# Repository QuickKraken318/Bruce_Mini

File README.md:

Original project: https://github.com/pr3y

Not tested IRL yet

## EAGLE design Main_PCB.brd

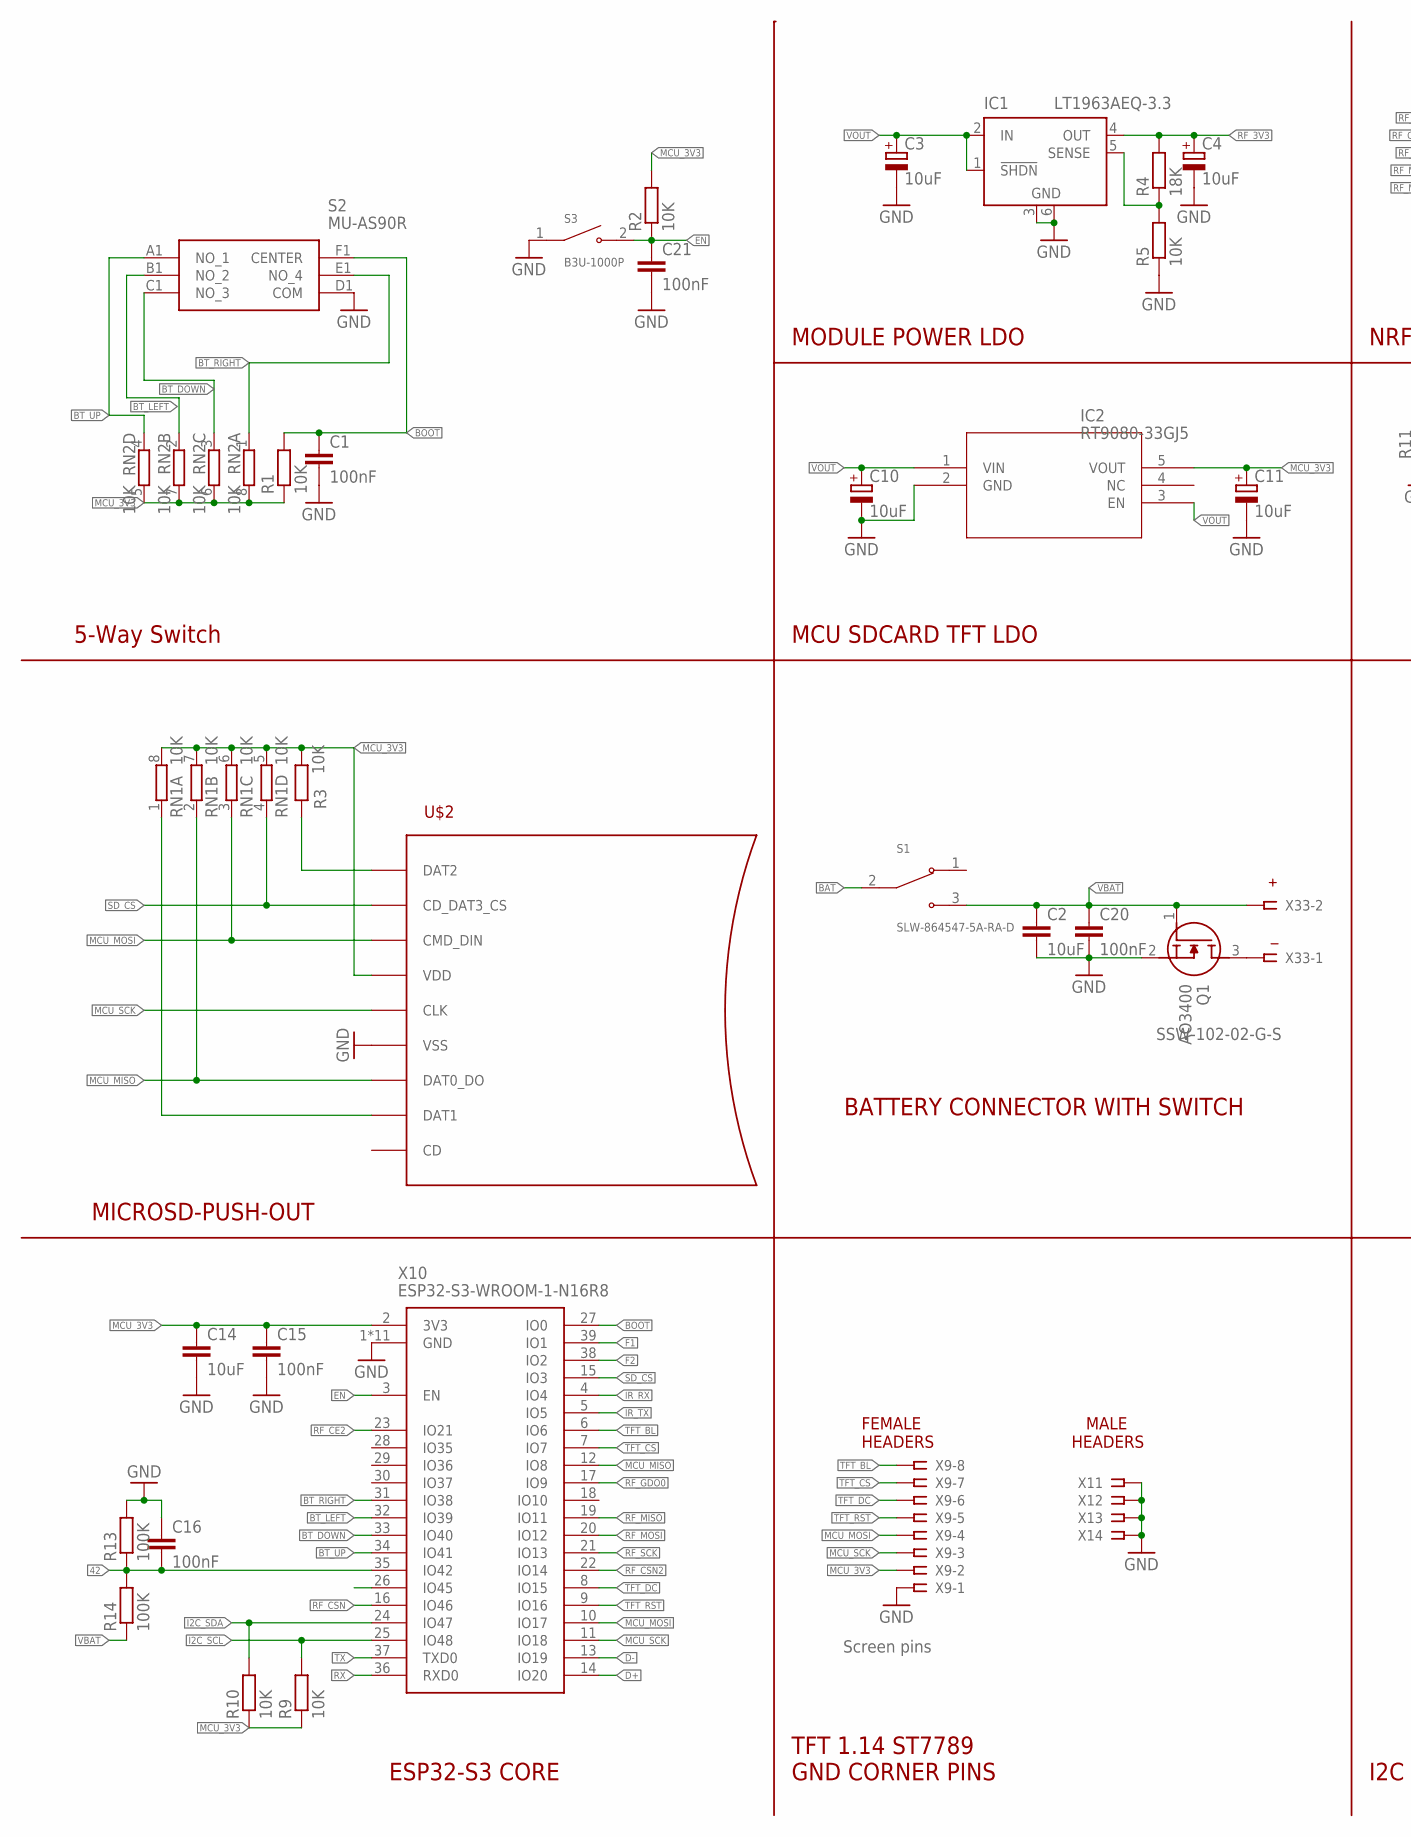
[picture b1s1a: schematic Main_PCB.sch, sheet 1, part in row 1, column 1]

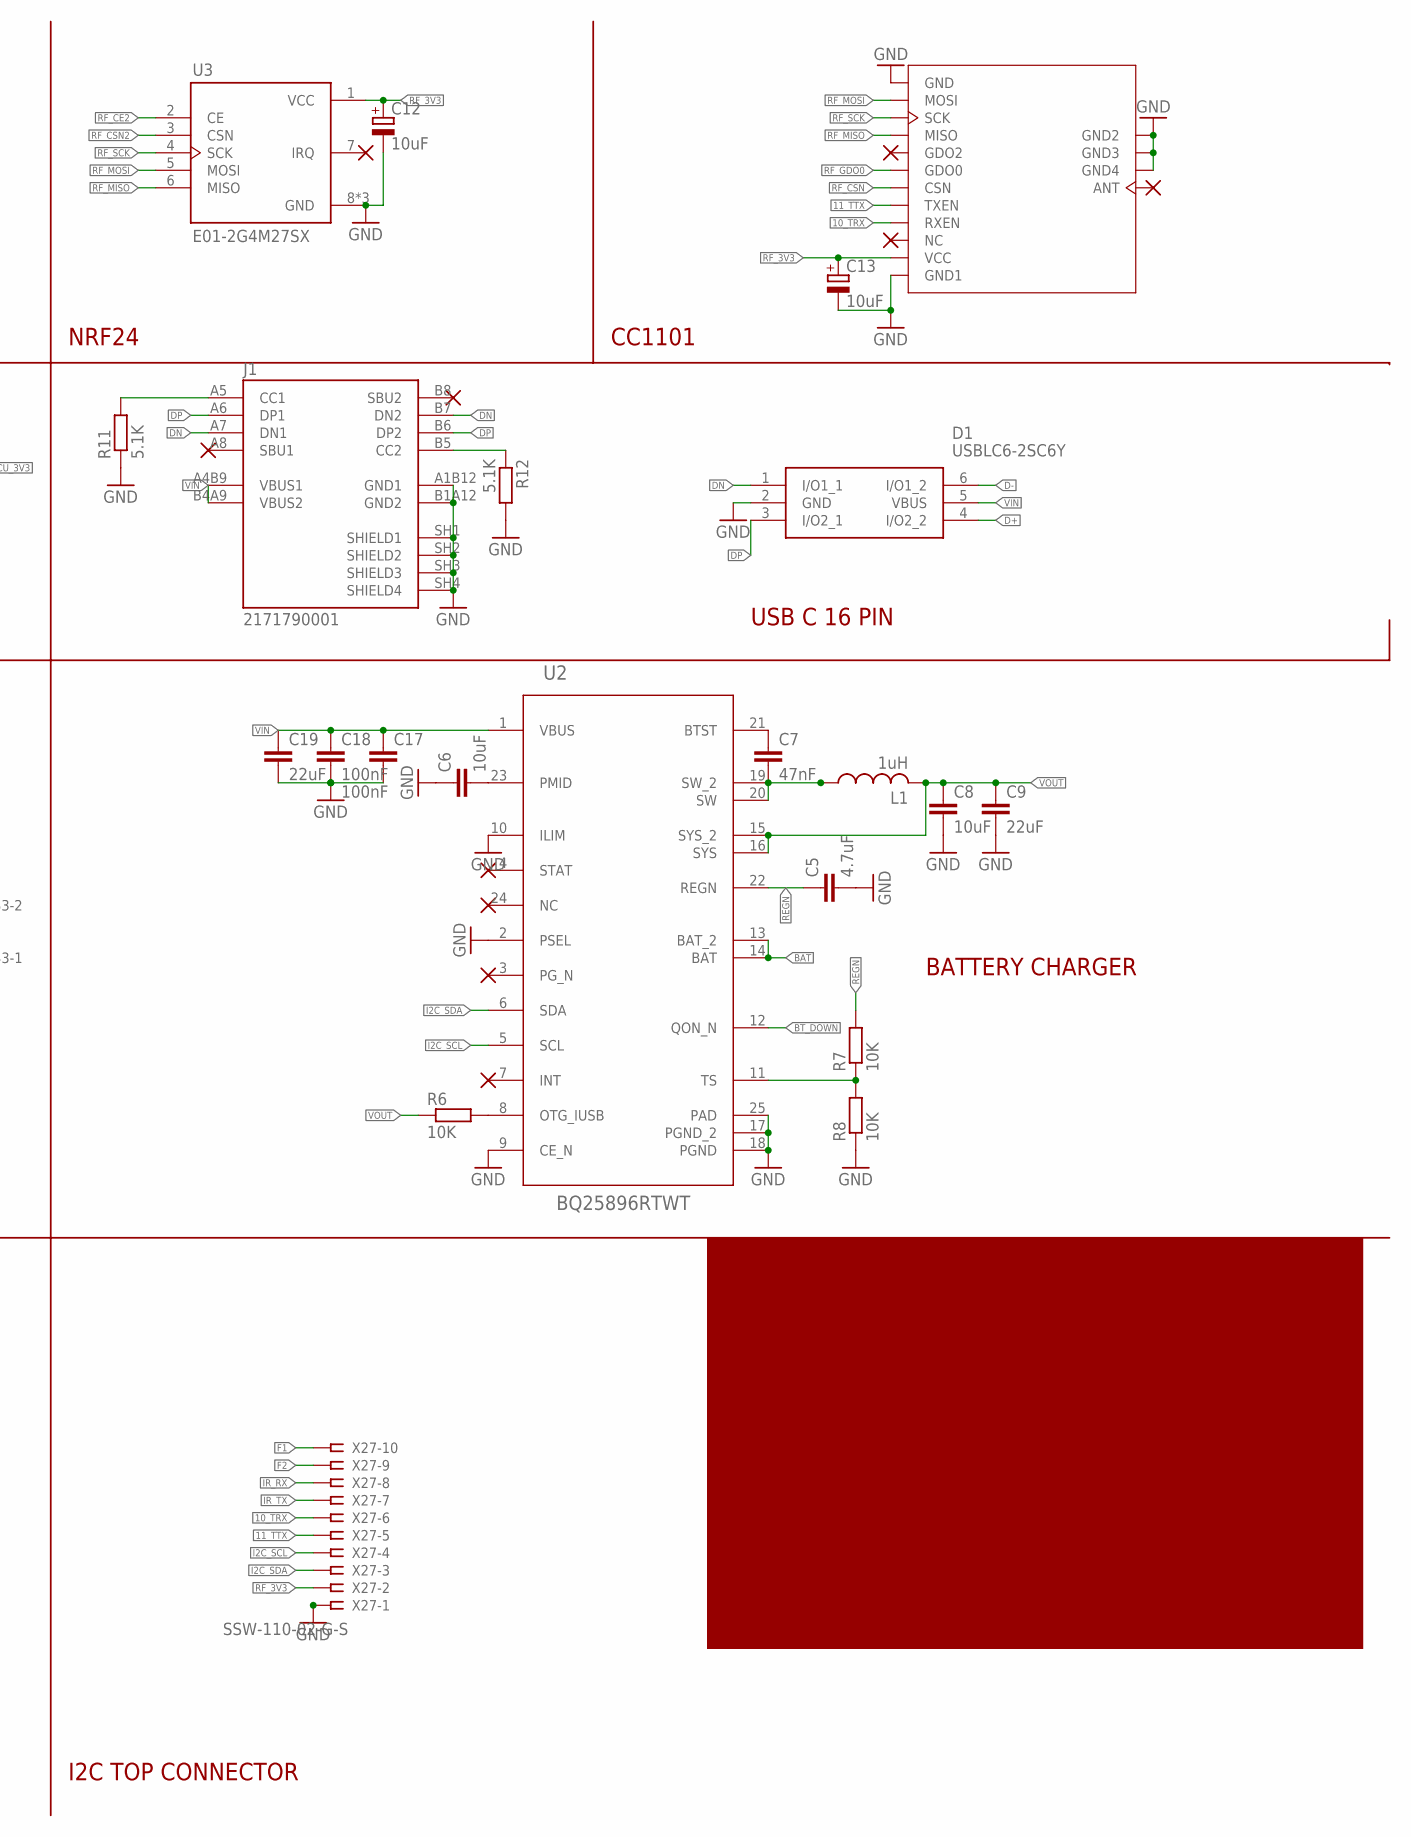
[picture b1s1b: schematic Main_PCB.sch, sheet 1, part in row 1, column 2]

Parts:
C1, C16, C17, C18, C20, C21: 100nF; C0603
C2, C6, C8: 10uF; C0603
C3, C4, C10, C11, C12, C13: 10uF; CT3216
C5: 4.7uF; C0603
C7: 47nF; C0603
C9, C19: 22uF; C0603
C14: 10uF; C1206
C15: 100nF; C1206
D1: USBLC6-2SC6Y; SOT95P280X145-6N
IC1: LT1963AEQ-3.3; Q5-DD
IC2: RT9080-33GJ5; TSOT-23-5_RIT
J1: 2171790001; MOLEX_2171790001
L1: 1uH; L4035M
Q1: AO3400; SOT95P280X125-3N
R1, R2, R3, R5, R6, R7, R8, R9, R10: 10K; R0603
R4: 18K; R0603
R11, R12: 5.1K; R0603
R13, R14: 100K; R0603
RN1, RN2: 10K; 0603-ARV
S1: SLW-864547-5A-RA-D; SW_SLW-864547-5A-RA-D
S2: MU-AS90R; MUAS90R
S3: B3U-1000P; SW_B3U-1000P
U2: BQ25896RTWT; RTW0024H
U3: E01-2G4M27SX; XCVR_E01-2G4M27SX
U4: PE07-433M20S
U$2: MICROSD-PUSH-OUT
X9: Screen pins; SSW-108-02-G-S
X10: ESP32-S3-WROOM-1-N16R8; ESP32S3WROOM1N8R2
X11, X12, X13, X14: SSW-101-02-G-S
X27: SSW-110-02-G-S
X33: SSW-102-02-G-S

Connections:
10_TRX: U4.RXEN, X27.6
11_TTX: U4.TXEN, X27.5
42: C16.2, R13.1, R14.2, X10.35 (IO42)
BAT: S1.2, U2.13 (BAT_2), U2.14 (BAT)
BOOT: C1.1, R1.2, S2.F1 (CENTER), X10.27 (IO0)
BT_DOWN: RN2.3 (1), S2.C1 (NO_3), U2.12 (QON_N), X10.33 (IO40)
BT_LEFT: RN2.2 (1), S2.B1 (NO_2), X10.32 (IO39)
BT_RIGHT: RN2.1, S2.E1 (NO_4), X10.31 (IO38)
BT_UP: RN2.4 (1), S2.A1 (NO_1), X10.34 (IO41)
D+: D1.4 (I/O2_2), X10.14 (IO20)
D-: D1.6 (I/O1_2), X10.13 (IO19)
DN: D1.1 (I/O1_1), J1.A7 (DN1), J1.B7 (DN2)
DP: D1.3 (I/O2_1), J1.A6 (DP1), J1.B6 (DP2)
EN: C21.1, R2.1, S3.2, X10.3 (EN)
F1: X10.39 (IO1), X27.10
F2: X10.38 (IO2), X27.9
GND: C1.2, C2.2, C3.-, C4.-, C5.2, C6.1, C8.2, C9.2, C10.-, C11.-, C12.-, C13.-, C14.2, C15.2, C16.1, C17.2, C18.2, C19.2, C20.2, C21.2, D1.2 (GND), IC1.3 (GND), IC1.6 (GND), IC2.2 (GND), J1.A1B12 (GND1), J1.B1A12 (GND2), J1.SH1 (SHIELD1), J1.SH2 (SHIELD2), J1.SH3 (SHIELD3), J1.SH4 (SHIELD4), Q1.2 (S), R5.1, R8.1, R11.1, R12.2, R13.2, S2.D1 (COM), S3.1, U2.2 (PSEL), U2.9 (CE_N), U2.10 (ILIM), U2.17 (PGND_2), U2.18 (PGND), U2.25 (PAD), U3.8 (GND), U3.9 (GND), U3.10 (GND), U4.GND, U4.GND1, U4.GND2, U4.GND3, U4.GND4, U$2.6 (VSS), U$2.G1 (VSS), U$2.G2 (VSS), U$2.G3 (VSS), U$2.G4 (VSS), X9.1, X10.1 (GND), X10.40 (GND), X10.41 (GND), X10.42 (GND), X10.43 (GND), X10.44 (GND), X10.45 (GND), X10.46 (GND), X10.47 (GND), X10.48 (GND), X10.49 (GND), X11.1, X12.1, X13.1, X14.1, X27.1; also elsewhere on the board
I2C_SCL: R9.2, U2.5 (SCL), X10.25 (IO48), X27.4
I2C_SDA: R10.2, U2.6 (SDA), X10.24 (IO47), X27.3
IR_RX: X10.4 (IO4), X27.8
IR_TX: X10.5 (IO5), X27.7
MCU_3V3: C11.+, C14.1, C15.1, IC2.5 (VOUT), R1.1, R2.2, R3.2, R9.1, R10.1, RN1.5 (2), RN1.6 (2), RN1.7 (2), RN1.8 (2), RN2.5 (2), RN2.6 (2), RN2.7 (2), RN2.8 (2), U$2.4 (VDD), X9.2, X10.2 (3V3)
MCU_MISO: RN1.2 (1), U$2.7 (DAT0_DO), X10.12 (IO8)
MCU_MOSI: RN1.3 (1), U$2.3 (CMD_DIN), X9.4, X10.10 (IO17)
MCU_SCK: U$2.5 (CLK), X9.3, X10.11 (IO18)
unnamed: J1.A5 (CC1), R11.2
unnamed: J1.B5 (CC2), R12.1
unnamed: R3.1, U$2.1 (DAT2)
unnamed: Q1.3 (D), X33.1
unnamed: RN1.1, U$2.8 (DAT1)
unnamed: IC1.5 (SENSE), R4.1, R5.2
unnamed: C7.1, U2.21 (BTST)
unnamed: C7.2, L1.1, U2.19 (SW_2), U2.20 (SW)
unnamed: R6.2, U2.8 (OTG_IUSB)
unnamed: R7.1, R8.2, U2.11 (TS)
unnamed: C6.2, U2.23 (PMID)
REGN: C5.1, R7.2, U2.22 (REGN)
RF_3V3: C4.+, C12.+, C13.+, IC1.4 (OUT), R4.2, U3.1 (VCC), U4.VCC, X27.2
RF_CE2: U3.2 (CE), X10.23 (IO21)
RF_CSN: U4.CSN, X10.16 (IO46)
RF_CSN2: U3.3 (CSN), X10.22 (IO14)
RF_GDO0: U4.GDO0, X10.17 (IO9)
RF_MISO: U3.6 (MISO), U4.MISO, X10.19 (IO11)
RF_MOSI: U3.5 (MOSI), U4.MOSI, X10.20 (IO12)
RF_SCK: U3.4 (SCK), U4.SCK, X10.21 (IO13)
RX: X10.36 (RXD0)
SD_CS: RN1.4 (1), U$2.2 (CD_DAT3_CS), X10.15 (IO3)
TFT_BL: X9.8, X10.6 (IO6)
TFT_CS: X9.7, X10.7 (IO7)
TFT_DC: X9.6, X10.8 (IO15)
TFT_RST: X9.5, X10.9 (IO16)
TX: X10.37 (TXD0)
VBAT: C2.1, C20.1, Q1.1 (G), R14.1, S1.3, X33.2
VIN: C17.1, C18.1, C19.1, D1.5 (VBUS), J1.A4B9 (VBUS1), J1.B4A9 (VBUS2), U2.1 (VBUS)
VOUT: C3.+, C8.1, C9.1, C10.+, IC1.1 (!SHDN), IC1.2 (IN), IC2.1 (VIN), IC2.3 (EN), L1.2, R6.1, U2.15 (SYS_2), U2.16 (SYS)

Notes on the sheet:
ESP32-S3 CORE
5-Way Switch
BATTERY CONNECTOR WITH SWITCH
MODULE POWER LDO
MCU SDCARD TFT LDO
TFT 1.14 ST7789 GND CORNER PINS
BATTERY CHARGER
USB C 16 PIN
CC1101
NRF24
FEMALE HEADERS
MALE HEADERS
I2C TOP CONNECTOR

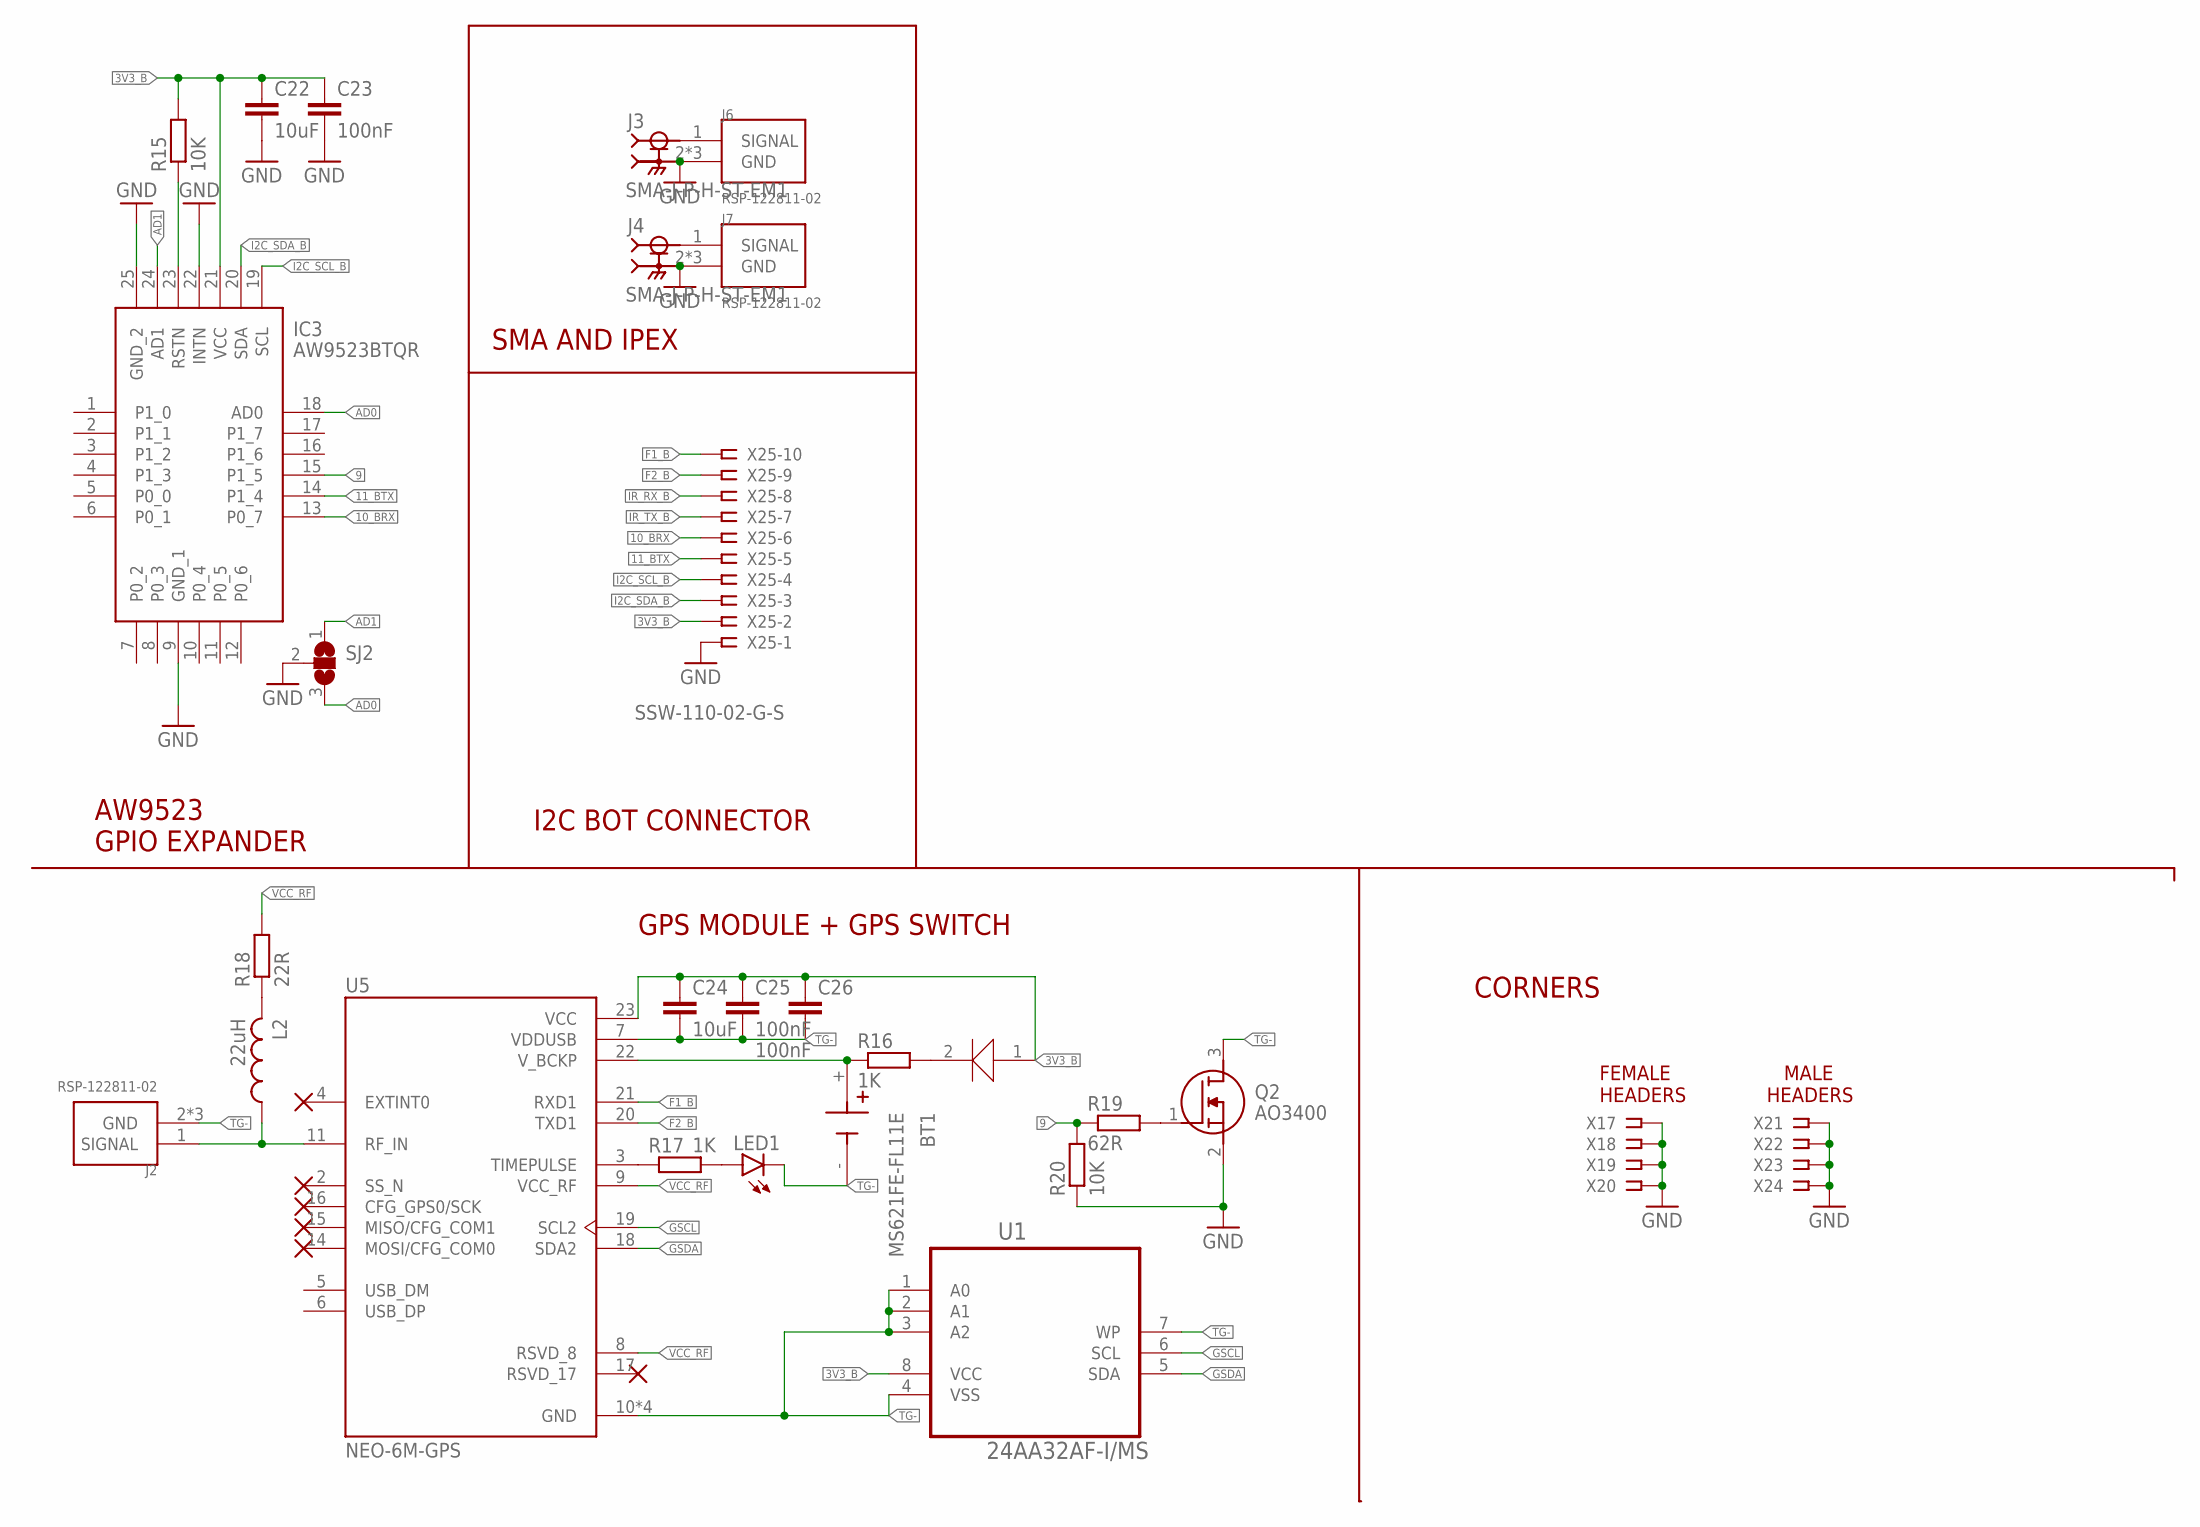
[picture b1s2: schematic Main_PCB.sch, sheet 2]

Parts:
BT1: MS621FE-FL11E; BAT_MS621FE-FL11E
C22, C24: 10uF; C0603
C23, C25, C26: 100nF; C0603
IC3: AW9523BTQR; QFN50P400X400X80-25N
J2, J6, J7: RSP-122811-02; SAMTEC_RSP-122811-02
J3, J4: SMA-J-P-H-ST-EM1; SAMTEC_SMA-J-P-H-ST-EM1
L2: 22uH; L3225P
LED1: LEDCHIP-LED0805; CHIP-LED0805
Q2: AO3400; SOT95P280X125-3N
R15, R20: 10K; R0603
R16, R17: 1K; R0603
R18: 22R; R0603
R19: 62R; R0603
SJ2: SJ2W; SJ_2
U1: 24AA32AF-I/MS; SOP65P490X110-8N
U5: NEO-6M-GPS; XCVR_NEO-6M-GPS
U$1: 5817SMJ_TR13; DIOM5336X250N
X17, X18, X19, X20, X21, X22, X23, X24: SSW-101-02-G-S
X25: SSW-110-02-G-S

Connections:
3V3_B: C22.1, C23.1, C24.1, C25.1, C26.1, IC3.21 (VCC), R15.2, U1.8 (VCC), U5.23 (VCC), U$1.1, X25.2
9: IC3.15 (P1_5), R19.1, R20.2
10_BRX: IC3.13 (P0_7), X25.6
11_BTX: IC3.14 (P1_4), X25.5
AD0: IC3.18 (AD0), SJ2.3
AD1: IC3.24 (AD1), SJ2.1
F1_B: U5.21 (RXD1), X25.10
F2_B: U5.20 (TXD1), X25.9
GND: C22.2, C23.2, IC3.9 (GND_1), IC3.22 (INTN), IC3.25 (GND_2), J3.2_1 (2), J3.2_2 (2), J3.3_1 (2), J3.3_2 (2), J4.2_1 (2), J4.2_2 (2), J4.3_1 (2), J4.3_2 (2), J6.2 (GND), J6.3 (GND), J6.4 (GND), J7.2 (GND), J7.3 (GND), J7.4 (GND), Q2.2 (S), R20.1, SJ2.2, X17.1, X18.1, X19.1, X20.1, X21.1, X22.1, X23.1, X24.1, X25.1; also elsewhere on the board
GSCL: U1.6 (SCL), U5.19 (SCL2)
GSDA: U1.5 (SDA), U5.18 (SDA2)
I2C_SCL_B: IC3.19 (SCL), X25.4
I2C_SDA_B: IC3.20 (SDA), X25.3
IR_RX_B: X25.8
IR_TX_B: X25.7
unnamed: BT1.+, R16.1, U5.22 (V_BCKP)
unnamed: R17.1, U5.3 (TIMEPULSE)
unnamed: LED1.A, R17.2
unnamed: R16.2, U$1.2
unnamed: J2.1 (SIGNAL), L2.1, U5.11 (RF_IN)
unnamed: IC3.23 (RSTN), R15.1
unnamed: L2.2, R18.1
unnamed: Q2.1 (G), R19.2
unnamed: J3.1, J6.1 (SIGNAL)
unnamed: J4.1, J7.1 (SIGNAL)
TG-: BT1.-, C24.2, C25.2, C26.2, J2.2 (GND), J2.3 (GND), J2.4 (GND), LED1.C, Q2.3 (D), U1.1 (A0), U1.2 (A1), U1.3 (A2), U1.4 (VSS), U1.7 (WP), U5.7 (VDDUSB), U5.10 (GND), U5.12 (GND), U5.13 (GND), U5.24 (GND)
VCC_RF: R18.2, U5.8 (RSVD_8), U5.9 (VCC_RF)

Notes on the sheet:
FEMALE HEADERS
MALE HEADERS
I2C BOT CONNECTOR
AW9523 GPIO EXPANDER
SMA AND IPEX
GPS MODULE + GPS SWITCH
CORNERS

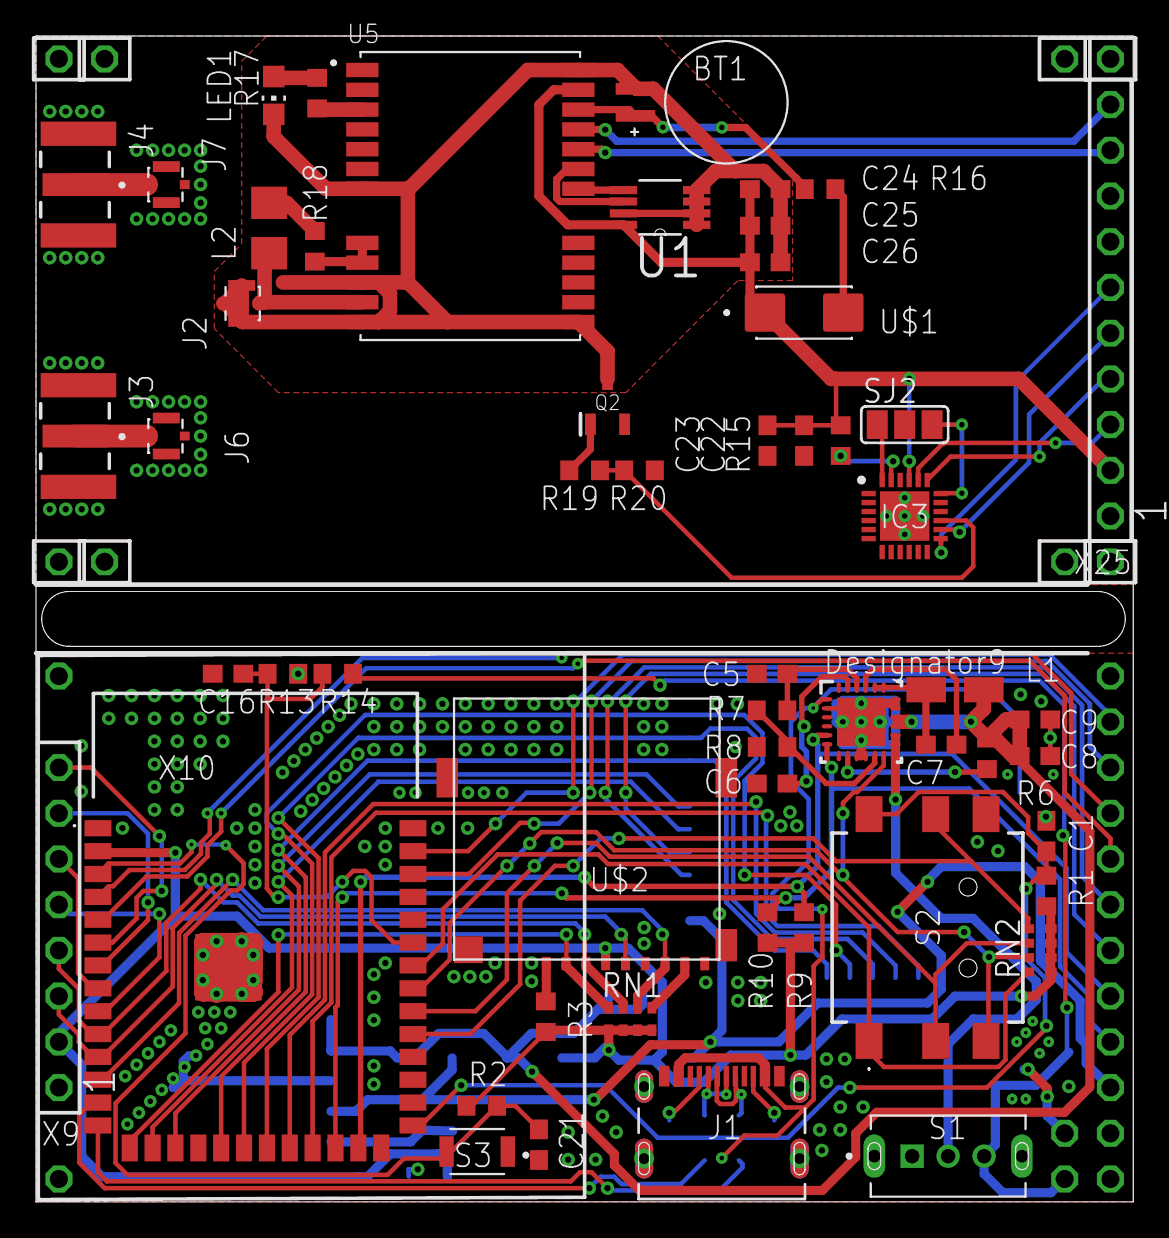
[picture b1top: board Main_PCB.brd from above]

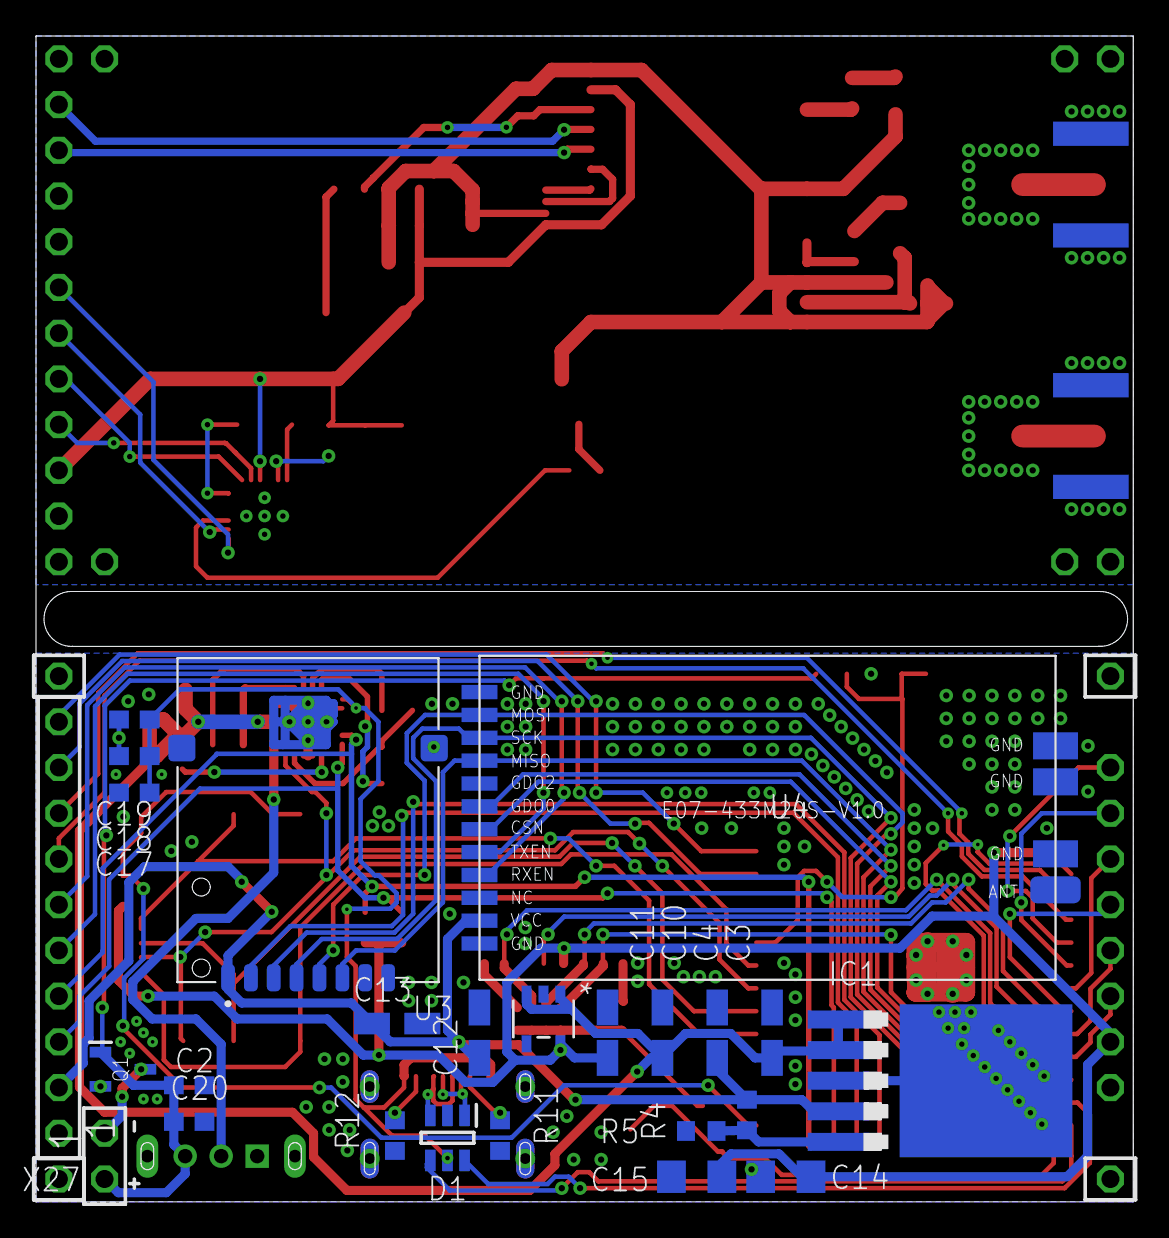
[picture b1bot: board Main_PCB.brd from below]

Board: 2 copper layers, 61.0 x 64.8 mm, 92 parts (29 on the bottom side), 77 nets.

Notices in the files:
parts and their libraries:
COPYRIGHT: Copyright (C) 2025 Ultra Librarian. All rights reserved.
